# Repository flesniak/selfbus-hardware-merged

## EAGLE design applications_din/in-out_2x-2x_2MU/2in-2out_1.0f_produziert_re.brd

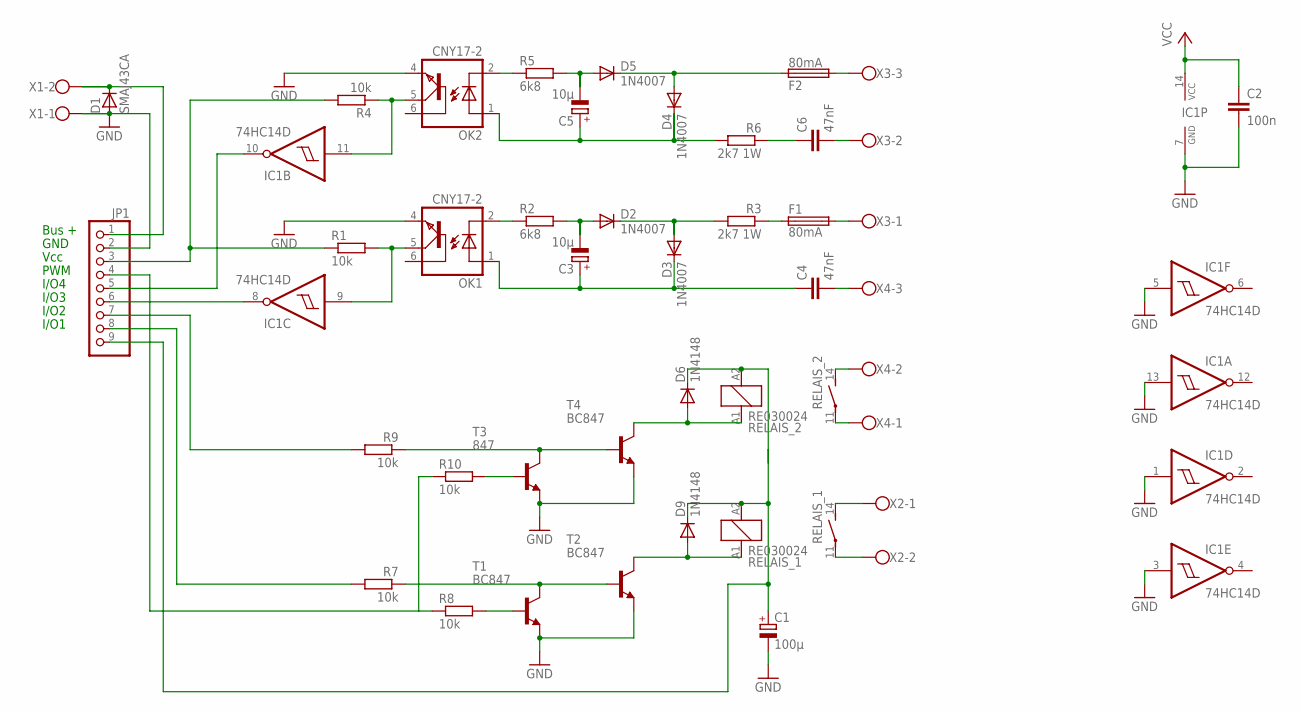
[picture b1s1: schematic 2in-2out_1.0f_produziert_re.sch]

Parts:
C1: 100µ; E3,5-8
C2: 100n; C1206
C3, C5: 10µ; E2-4
C4, C6: 47nF; C075-063X106
D1: SMAJ43CA; SMB
D2, D3, D4, D5: 1N4007; D-2.5
D6, D9: 1N4148; MINIMELF
F1, F2: 80mA; 0617V
IC1: 74HC14D; SO14
JP1: PINHD-1X9; 1X09
OK1, OK2: CNY17-2; DIL06
R1, R4, R7, R8, R9, R10: 10k; M1206
R2, R5: 6k8; 0207/2V
R3, R6: 2k7 1W; 0207/2V
RELAIS_1, RELAIS_2: RE030024; RE-SCHRACK
T1, T2, T4: BC847; SOT23
T3: 847; SOT23
X1, X2: W237-02P; W237-132
X3, X4: W237-3E

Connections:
EIB+: D1.1 (C), JP1.1, X1.2
GND: C1.-, C2.2, D1.2 (A), IC1.1 (I), IC1.3 (I), IC1.5 (I), IC1.7 (GND), IC1.13 (I), JP1.2, OK1.4 (EMI), OK2.4 (EMI), T1.2 (E), T2.2 (E), T3.2 (E), T4.2 (E), X1.1
IO1: JP1.7, R9.2
IO2: JP1.8, R7.2
IO3: IC1.8 (O), JP1.6
IO4: IC1.10 (O), JP1.5
unnamed: OK1.2 (C), R2.1
unnamed: RELAIS_1.11, X2.2
unnamed: C3.-, D2.A, R2.2
unnamed: D2.C, D3.A, R3.2
unnamed: RELAIS_1.14 (S), X2.1
unnamed: F1.1, R3.1
unnamed: RELAIS_2.14 (S), X4.2
unnamed: RELAIS_2.11, X4.1
unnamed: OK2.2 (C), R5.1
unnamed: C6.1, R6.1
unnamed: F2.2, X3.3
unnamed: C5.-, D5.A, R5.2
unnamed: R7.1, T1.3 (C), T2.1 (B)
unnamed: C4.2, X4.3
unnamed: R9.1, T3.3 (C), T4.1 (B)
unnamed: D4.A, D5.C, F2.1
unnamed: D6.A, RELAIS_2.A1 (1), T4.3 (C)
unnamed: C5.+, D4.C, OK2.1 (A), R6.2
unnamed: R8.2, T1.1 (B)
unnamed: R10.2, T3.1 (B)
unnamed: C3.+, C4.1, D3.C, OK1.1 (A)
unnamed: C6.2, X3.2
unnamed: F1.2, X3.1
unnamed: IC1.11 (I), OK2.5 (COL), R4.1
unnamed: IC1.9 (I), OK1.5 (COL), R1.2
PWM: JP1.4, R8.1, R10.1
R3: D9.A, RELAIS_1.A1 (1), T2.3 (C)
VCC: C2.1, IC1.14 (VCC), JP1.3, R1.1, R4.2
VDD_IN: C1.+, D6.C, D9.C, JP1.9, RELAIS_1.A2 (2), RELAIS_2.A2 (2)

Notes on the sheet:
Bus +
GND
Vcc
PWM
I/O4
I/O3
I/O2
I/O1

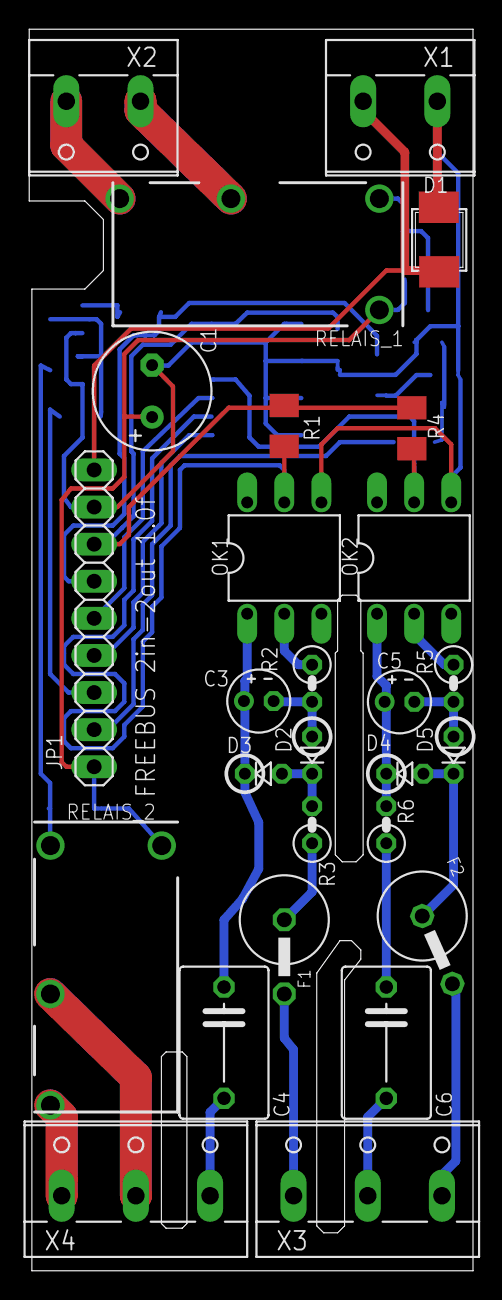
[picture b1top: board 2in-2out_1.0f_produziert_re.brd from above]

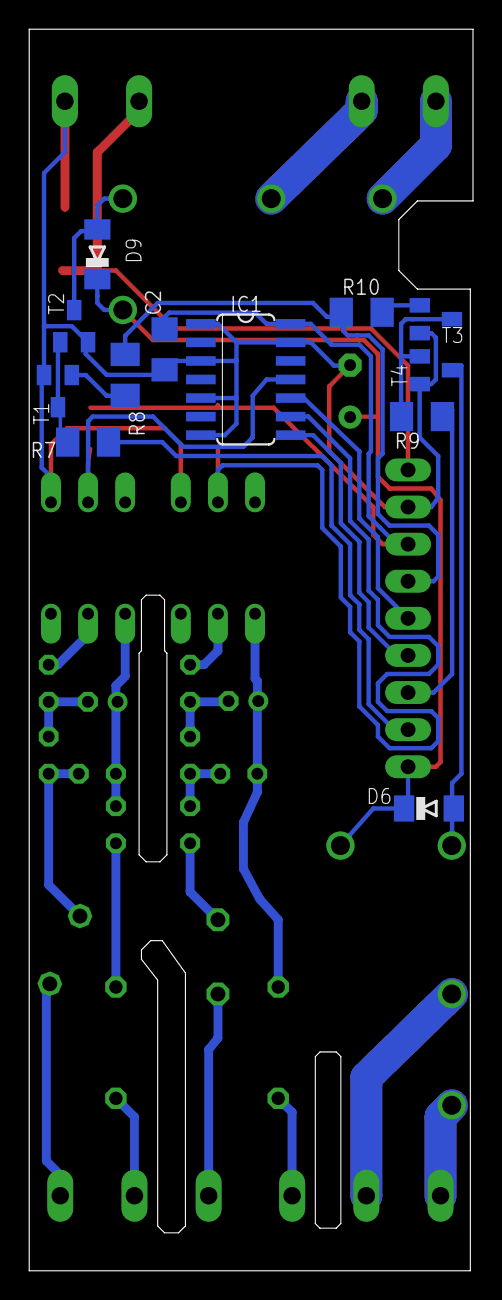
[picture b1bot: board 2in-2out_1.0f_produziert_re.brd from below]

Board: 2 copper layers, 30.4 x 85.0 mm, 39 parts (12 on the bottom side), 35 nets.

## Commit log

2024-06-02 update in-out_4x-2x_2MU - final for now
2024-06-02 add global kicad symbol & footprint libs
2024-06-02 out 8x 16A bistab 4MU is now v2.3.0 kicad
2024-06-02 update controller_lpc1115_2MU_v1.04 - final for now
2024-06-02 just all all projects for backup
2024-06-02 add leds_buttons_lpc1115ctrl_2MU
    WIP
2024-06-02 update HFE20 footprint, add BS11, CNMB_4
2024-06-02 add WIP kicad version of controller_lpc1115_2MU_v1.04
2024-06-02 add LPC1115_4TE_TOP - final for now
2024-06-02 fixup! properly rename 4in-2out application & top projects
2024-06-02 add 2in-2out_2.0
    mostly finished
2024-06-02 properly rename 4in-2out application & top projects
2024-06-02 update out_8x_16A_bistab_4MU_v2.3.0_kicad - final for now
2024-06-02 add drill files
2024-06-02 add kicad backup/cache files to gitignore
2024-06-02 rename and move out 8x 16A bistab 2.1 kicad
2024-07-01 add kicad projects for bb_pwr_knx_v-measure and io-16x-fused-fm
    ...imported from eagle
2024-07-01 update all stuff
2024-07-28 add top_led_btn_2MU_TOP
2024-07-28 add controller_lpc1115_2MU_v1.04 gerbers
2024-07-28 add app_out_8x_16A_bistab_4MU_BOT_v2.0.0.kicad_sch
2024-07-28 add app_out_8x_16A_bistab_seperated_4MU_BOT_v2.0.0
2024-07-28 add remaining app_out_8x_16A_bistab_4MU_BOT_v2.0.0
2024-07-28 add top_led_btn_2MU_TOP gerbers - remove!
2024-07-28 drop 2in-2out_2.0/gerber_v2.0
2024-07-28 drop top_led_btn_2MU_TOP/gerber
2024-07-28 drop controller_lpc1115_2MU_v1.04/gerber_v2.0
2024-07-28 clean up controller_lpc1115_2MU_v1.04
2024-07-28 bb_pwr_knx_v-measure final
2024-07-28 io-16x-fused-fm: use micro-match from selfbus library
2024-07-28 bump bb_pwr_knx_v WIP
2024-07-28 fixups for 2MU/4MU controllers - use Seiko oszillator
2024-07-28 bump io-16x-fused-fm - conversion mostly done
2024-07-28 finally standardize selected parts on all boards
2024-07-28 convert io-16x-fused-fm WIP
2024-07-28 move controller_lpc1115_2MU_v1.04 to generic kicad folder
2024-07-28 update LPC1115_4TE_TOP
2024-07-28 update bb_pwr_knx_v-measure
2024-07-28 drop bom+gerber files of io-16x-fused-fm
2024-07-28 final for manufacturing
2024-07-28 update io-16x-fused-fm
2024-07-28 update in-out_4x-2x_2MU
2024-08-18 update xtal caps, eib_in cap+resistor, bus_v resistors
2024-08-18 rename controller_lpc1115_2MU_v1.04 -> lpc1115_2MU_MID
    version 2.01
2024-08-18 gitignore: ignore kicad fp-info-cache
2024-09-02 controllers: reduce osc load, fix DNP for voltage measurement
